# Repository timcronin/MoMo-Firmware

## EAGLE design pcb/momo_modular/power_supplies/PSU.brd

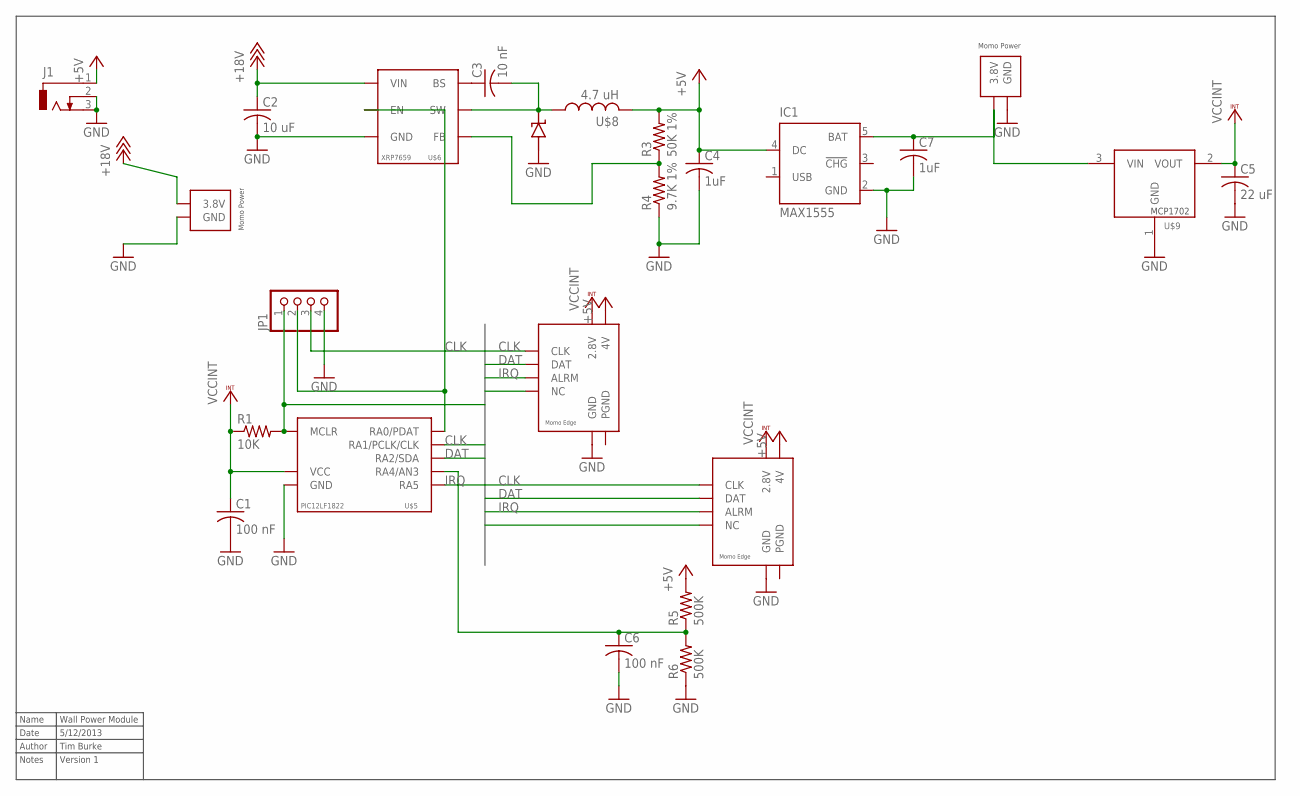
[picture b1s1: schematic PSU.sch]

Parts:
C1, C6: 100 nF; C0402
C2: 10 uF; C0805
C3: 10 nF; C0402
C4, C7: 1uF; C0402
C5: 22 uF; C0402
IC1: MAX1555; SOT23-5L
J1: DCJ0303
JP1: PINHD-1X4; 1X04
R1: 10K; R0603
R3: 50K 1%; R0603
R4: 9.7K 1%; R0603
R5, R6: 500K; R0603
U$1, U$2: MOMO-EDGE-POWER-M; MOMO-EDGE-SMALL-2M
U$5: PIC12LF1822; SOIC8
U$6: XRP7659; SOT23-6L
U$7: DIODE_SS2P3
U$8: 4.7 uH; NR6028-INDUCTOR
U$9: MCP1702; SOT23
U$10: MOMO-EDGE-8F
U$11: MOMO-EDGE-8M

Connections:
+5V: C4.1, IC1.4 (DC), J1.1, R3.2, R5.2, U$8.2, U$10.V4. (4V), U$11.V4 (4V)
+18V: C2.1, U$1.1 (3.8V), U$6.5 (VIN)
CLK: JP1.3, U$5.6 (RA1/PCLK/CLK), U$10.CLK, U$11.CLK
DAT: U$5.5 (RA2/SDA), U$10.DAT, U$11.DAT
GND: C1.2, C2.2, C4.2, C5.2, C6.2, C7.2, IC1.2 (GND), J1.2, J1.3, JP1.4, R4.1, R6.1, U$1.2 (GND), U$2.2 (GND), U$5.8 (GND), U$6.2 (GND), U$7.AN, U$9.1 (GND), U$10.GND, U$11.GND
IRQ: U$5.2 (RA5), U$10.ARLM (ALRM), U$11.ALRM
MCLR: JP1.1, R1.2, U$5.4 (MCLR), U$10.NV (NC), U$11.NC
unnamed: C7.1, IC1.5 (BAT), U$2.1 (3.8V), U$9.3 (VIN)
unnamed: C3.2, U$6.6 (SW), U$7.CATH, U$8.1
unnamed: C3.1, U$6.1 (BS)
unnamed: C6.1, R5.1, R6.2, U$5.3 (RA4/AN3)
unnamed: R3.1, R4.2, U$6.3 (FB)
unnamed: JP1.2, U$5.7 (RA0/PDAT), U$6.4 (EN)
PGND: U$10.PGND, U$11.PGND
VCCINT: C1.1, C5.1, R1.1, U$5.1 (VCC), U$9.2 (VOUT), U$10.V28 (2.8V), U$11.V28 (2.8V)

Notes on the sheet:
Name
Wall Power Module
Date
5/12/2013
Author
Tim Burke
Notes
Version 1

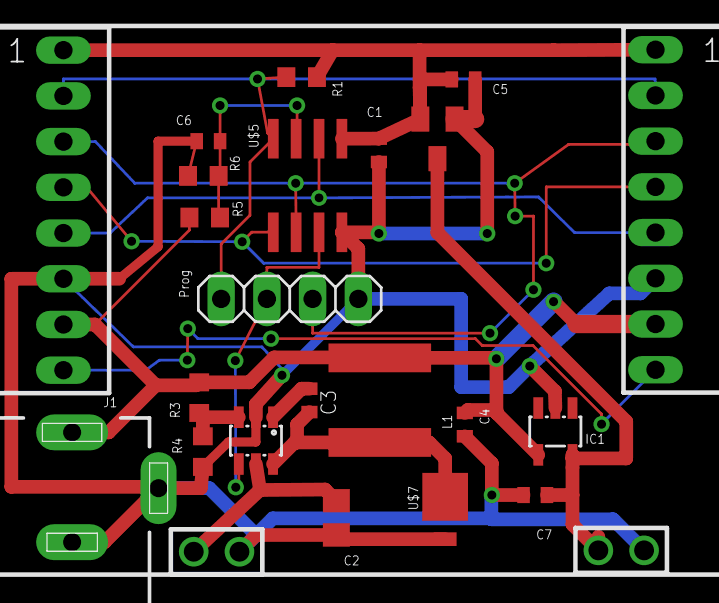
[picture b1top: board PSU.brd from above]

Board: 2 copper layers, 24 parts (0 on the bottom side), 15 nets.

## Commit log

2013-03-12 Makefile changes
    adds sensor files
2013-03-12 Debugging SPI
2013-03-14 Set next_free and next_read as local
2013-03-14 more experimentation with memory allocation
2013-03-18 Sensor code. not tested
2013-03-18 deleted emacs background
2013-03-20 Began implementing timer controls
2013-03-21 Working sensor pulse count. Not yet tested with real sensor
2013-03-22 Removed enable interrupts from configure_sensor
    put into sensor.c
2013-03-28 Started timer code
2013-03-30 Worked on timers
2013-03-31 uncommented debug stuff
2013-04-01 Added sensor task queueing to sensor.c
2013-04-02 Changed project to build with MPLAB
2013-04-03 Added sensor serial output
2013-04-03 Added sensor handlers. building
2013-07-22 Preliminary Designs for power supply board with wallplug and solar supplies, and battery charging capability
2013-07-22 Complete First draft of board layout
2013-07-22 Updated schematic and layout to reflect capacitor changes
